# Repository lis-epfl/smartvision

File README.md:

# smartvision
SmartVision sensor

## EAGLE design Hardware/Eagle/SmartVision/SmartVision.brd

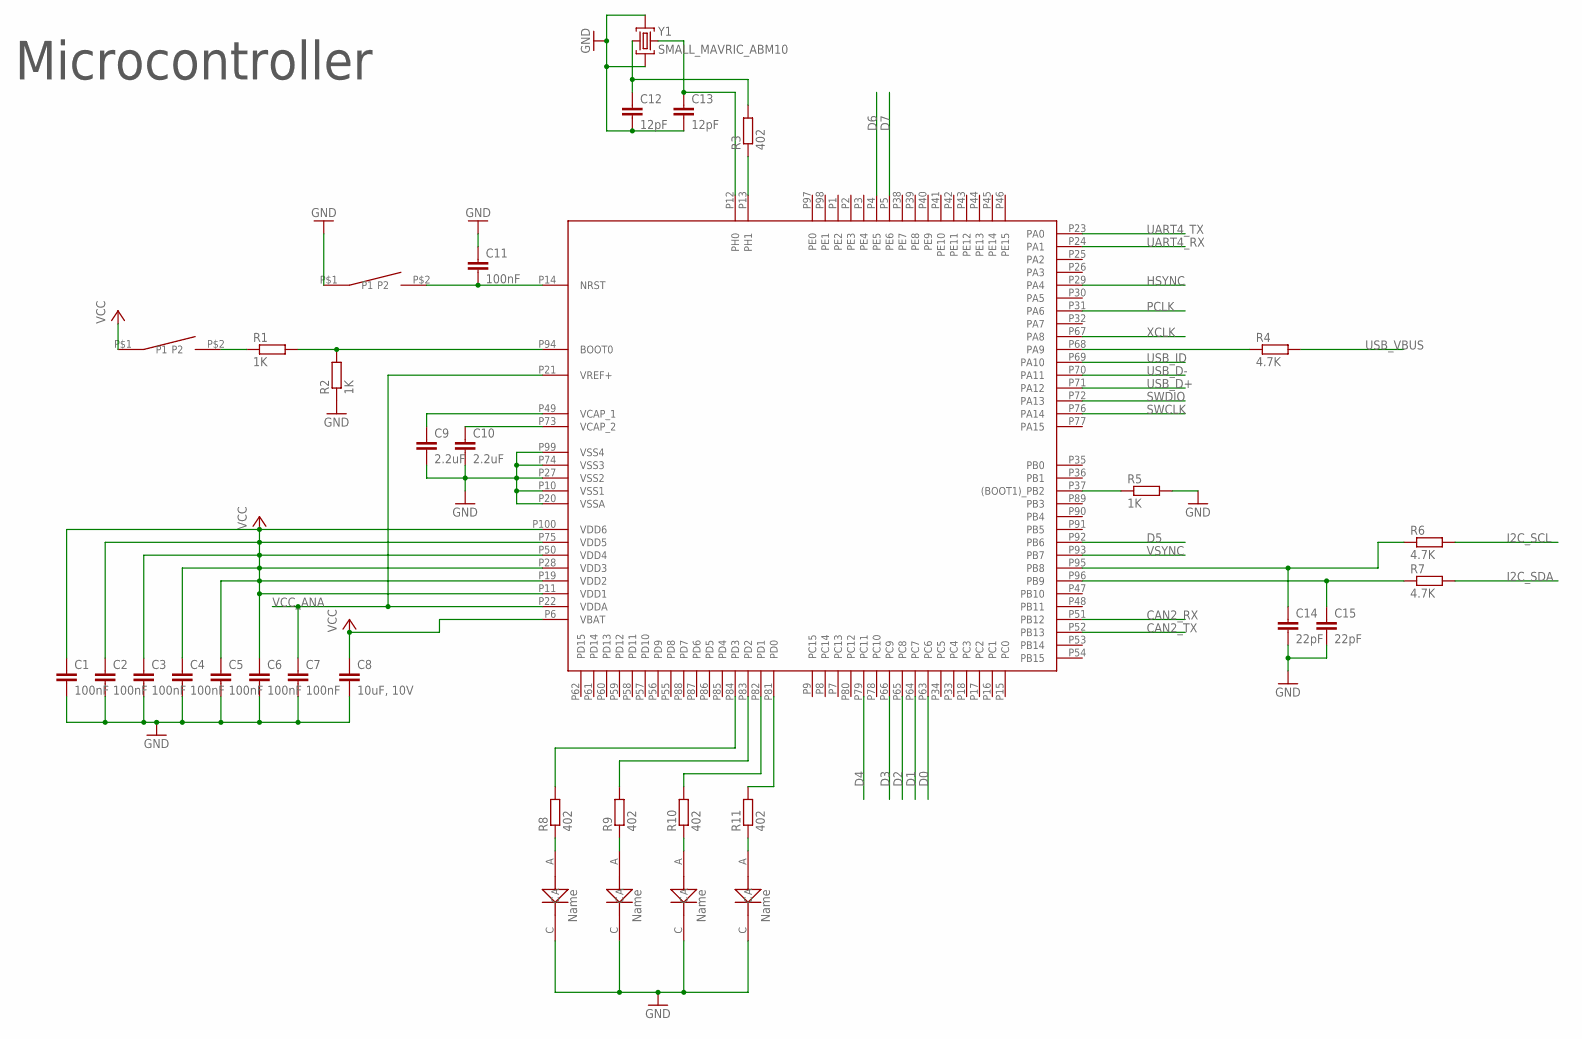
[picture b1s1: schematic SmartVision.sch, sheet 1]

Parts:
C1, C2, C3, C4, C5, C6, C7, C11: 100nF; SMALL_MAVRIC_SMALL_MAVRIC_CAPACITOR_C0402
C8: 10uF, 10V; SMALL_MAVRIC_SMALL_MAVRIC_CAPACITOR_C0603
C9, C10: 2.2uF; SMALL_MAVRIC_SMALL_MAVRIC_CAPACITOR_C0402
C12, C13: 12pF; SMALL_MAVRIC_SMALL_MAVRIC_CAPACITOR_C0402
C14, C15: 22pF; SMALL_MAVRIC_SMALL_MAVRIC_CAPACITOR_C0402
R1, R2, R5: 1K; SMALL_MAVRIC_SMALL_MAVRIC_RESISTOR_R0402
R3, R8, R9, R10, R11: 402; SMALL_MAVRIC_SMALL_MAVRIC_RESISTOR_R0402
R4, R6, R7: 4.7K; SMALL_MAVRIC_SMALL_MAVRIC_RESISTOR_R0402
U$1: STM32F407VGT6-100
U$29, U$31: SWITCH_OFF_(ON)
U$40, U$41, U$42, U$43: LED
Y1: SMALL_MAVRIC_ABM10; SMALL_MAVRIC_OSCILLATOR_ABM10

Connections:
CAN2_RX: U$1.P51 (PB12); also elsewhere on the board
CAN2_TX: U$1.P52 (PB13); also elsewhere on the board
D0: U$1.P63 (PC6); also elsewhere on the board
D1: U$1.P64 (PC7); also elsewhere on the board
D2: U$1.P65 (PC8); also elsewhere on the board
D3: U$1.P66 (PC9); also elsewhere on the board
D4: U$1.P79 (PC11); also elsewhere on the board
D5: U$1.P92 (PB6); also elsewhere on the board
D6: U$1.P4 (PE5); also elsewhere on the board
D7: U$1.P5 (PE6); also elsewhere on the board
GND: C1.2, C2.2, C3.2, C4.2, C5.2, C6.2, C7.2, C8.2, C9.2, C10.2, C11.1, C12.2, C13.2, C14.2, C15.2, R2.1, R5.2, U$1.P10 (VSS1), U$1.P20 (VSSA), U$1.P27 (VSS2), U$1.P74 (VSS3), U$1.P99 (VSS4), U$29.P$1 (P1), U$40.C, U$41.C, U$42.C, U$43.C, Y1.2, Y1.4; also elsewhere on the board
HSYNC: U$1.P29 (PA4); also elsewhere on the board
I2C_SCL: R6.2; also elsewhere on the board
I2C_SDA: R7.2; also elsewhere on the board
unnamed: R11.2, U$1.P81 (PD0)
unnamed: R10.2, U$1.P82 (PD1)
unnamed: R9.2, U$1.P83 (PD2)
unnamed: R8.2, U$1.P84 (PD3)
unnamed: C13.1, U$1.P12 (PH0), Y1.3
unnamed: R8.1, U$40.A
unnamed: C12.1, R3.2, Y1.1
unnamed: R9.1, U$41.A
unnamed: R10.1, U$42.A
unnamed: R3.1, U$1.P13 (PH1)
unnamed: C15.1, R7.1, U$1.P96 (PB9)
unnamed: C9.1, U$1.P49 (VCAP_1)
unnamed: C10.1, U$1.P73 (VCAP_2)
unnamed: C14.1, R6.1, U$1.P95 (PB8)
unnamed: R4.1, U$1.P68 (PA9)
unnamed: C11.2, U$1.P14 (NRST), U$29.P$2 (P2)
unnamed: R1.1, U$31.P$2 (P2)
unnamed: R1.2, R2.2, U$1.P94 (BOOT0)
unnamed: R5.1, U$1.P37 ((BOOT1)_PB2)
unnamed: R11.1, U$43.A
PCLK: U$1.P31 (PA6); also elsewhere on the board
SWCLK: U$1.P76 (PA14); also elsewhere on the board
SWDIO: U$1.P72 (PA13); also elsewhere on the board
UART4_RX: U$1.P24 (PA1); also elsewhere on the board
UART4_TX: U$1.P23 (PA0); also elsewhere on the board
USB_D+: U$1.P71 (PA12); also elsewhere on the board
USB_D-: U$1.P70 (PA11); also elsewhere on the board
USB_ID: U$1.P69 (PA10); also elsewhere on the board
USB_VBUS: R4.2; also elsewhere on the board
VCC: C1.1, C2.1, C3.1, C4.1, C5.1, C6.1, C8.1, U$1.P6 (VBAT), U$1.P11 (VDD1), U$1.P19 (VDD2), U$1.P28 (VDD3), U$1.P50 (VDD4), U$1.P75 (VDD5), U$1.P100 (VDD6), U$31.P$1 (P1); also elsewhere on the board
VCC_ANA: C7.1, U$1.P21 (VREF+), U$1.P22 (VDDA); also elsewhere on the board
VSYNC: U$1.P93 (PB7); also elsewhere on the board
XCLK: U$1.P67 (PA8); also elsewhere on the board

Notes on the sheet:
Microcontroller

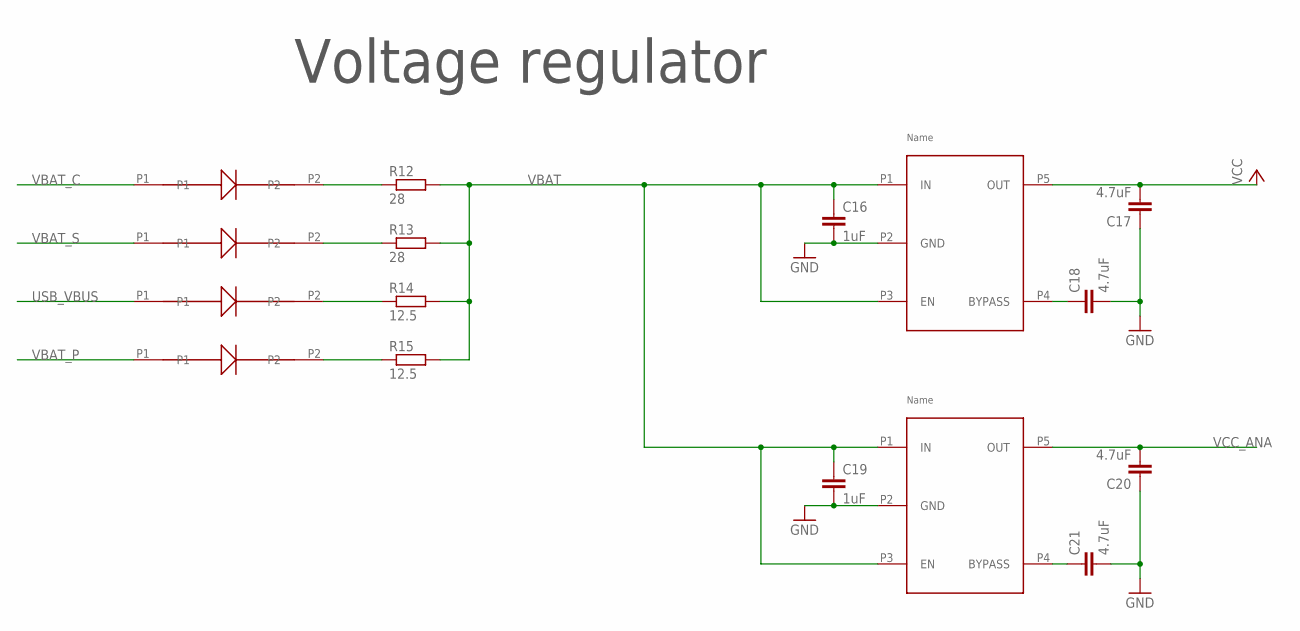
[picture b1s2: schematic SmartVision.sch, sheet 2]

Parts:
C16, C19: 1uF; SMALL_MAVRIC_SMALL_MAVRIC_CAPACITOR_C0402
C17, C18, C20, C21: 4.7uF; SMALL_MAVRIC_SMALL_MAVRIC_CAPACITOR_C0603
R12, R13: 28; SMALL_MAVRIC_SMALL_MAVRIC_RESISTOR_R0402
R14, R15: 12.5; SMALL_MAVRIC_SMALL_MAVRIC_RESISTOR_R0402
U$2, U$7: VOLTAGE_REGULATOR_3V
U$54, U$55, U$57, U$61: DIODE_SCHOTTKY

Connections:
GND: C16.2, C17.1, C18.2, C19.2, C20.1, C21.2, U$2.P2 (GND), U$7.P2 (GND); also elsewhere on the board
unnamed: C21.1, U$7.P4 (BYPASS)
unnamed: C18.1, U$2.P4 (BYPASS)
unnamed: R13.1, U$61.P2
unnamed: R15.1, U$54.P2
unnamed: R12.1, U$55.P2
unnamed: R14.1, U$57.P2
USB_VBUS: U$57.P1; also elsewhere on the board
VBAT: C16.1, C19.1, R12.2, R13.2, R14.2, R15.2, U$2.P1 (IN), U$2.P3 (EN), U$7.P1 (IN), U$7.P3 (EN); also elsewhere on the board
VBAT_C: U$55.P1; also elsewhere on the board
VBAT_P: U$54.P1; also elsewhere on the board
VBAT_S: U$61.P1; also elsewhere on the board
VCC: C17.2, U$2.P5 (OUT); also elsewhere on the board
VCC_ANA: C20.2, U$7.P5 (OUT); also elsewhere on the board

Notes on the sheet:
Voltage regulator

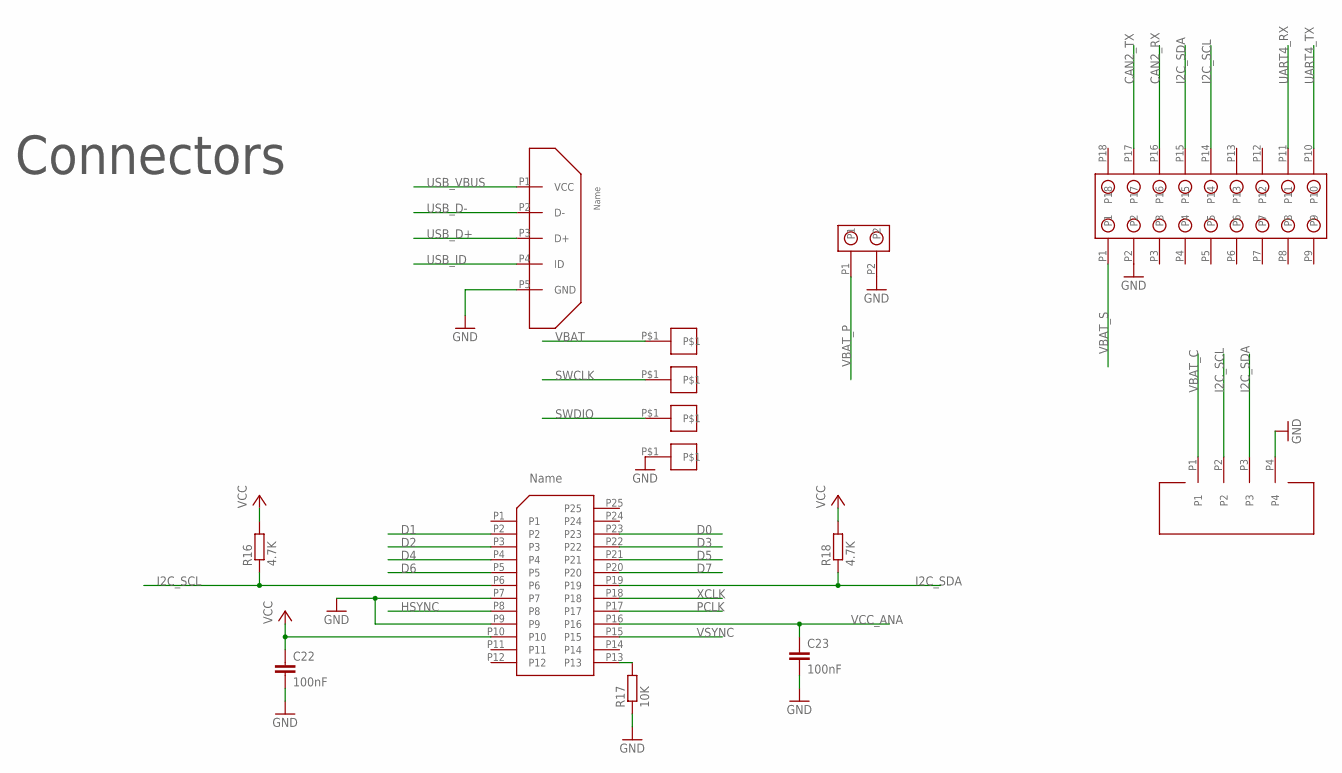
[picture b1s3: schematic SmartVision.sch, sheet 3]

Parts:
C22, C23: 100nF; SMALL_MAVRIC_SMALL_MAVRIC_CAPACITOR_C0402
R16, R18: 4.7K; SMALL_MAVRIC_SMALL_MAVRIC_RESISTOR_R0402
R17: 10K; SMALL_MAVRIC_SMALL_MAVRIC_RESISTOR_R0402
U$3, U$5, U$63, U$64: PAD_FLASH
U$4: MICRO_USB_PLUG
U$11: CON_CAMERA_FPC_25P_0.3MM
U$52: CON_2.54MM_18PINS_STACKABLE
U$53: CON_1.25MM_4PINS
U$59: CON_2.54MM_2PINS

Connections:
CAN2_RX: U$52.P16; also elsewhere on the board
CAN2_TX: U$52.P17; also elsewhere on the board
D0: U$11.P23; also elsewhere on the board
D1: U$11.P2; also elsewhere on the board
D2: U$11.P3; also elsewhere on the board
D3: U$11.P22; also elsewhere on the board
D4: U$11.P4; also elsewhere on the board
D5: U$11.P21; also elsewhere on the board
D6: U$11.P5; also elsewhere on the board
D7: U$11.P20; also elsewhere on the board
GND: C22.2, C23.2, R17.1, U$3.P$1, U$4.P5 (GND), U$11.P7, U$11.P9, U$52.P2, U$53.P4, U$59.P2; also elsewhere on the board
HSYNC: U$11.P8; also elsewhere on the board
I2C_SCL: R16.1, U$11.P6, U$52.P14, U$53.P2; also elsewhere on the board
I2C_SDA: R18.1, U$11.P19, U$52.P15, U$53.P3; also elsewhere on the board
unnamed: R17.2, U$11.P13
PCLK: U$11.P17; also elsewhere on the board
SWCLK: U$63.P$1; also elsewhere on the board
SWDIO: U$64.P$1; also elsewhere on the board
UART4_RX: U$52.P11; also elsewhere on the board
UART4_TX: U$52.P10; also elsewhere on the board
USB_D+: U$4.P3 (D+); also elsewhere on the board
USB_D-: U$4.P2 (D-); also elsewhere on the board
USB_ID: U$4.P4 (ID); also elsewhere on the board
USB_VBUS: U$4.P1 (VCC); also elsewhere on the board
VBAT: U$5.P$1; also elsewhere on the board
VBAT_C: U$53.P1; also elsewhere on the board
VBAT_P: U$59.P1; also elsewhere on the board
VBAT_S: U$52.P1; also elsewhere on the board
VCC: C22.1, R16.2, R18.2, U$11.P10; also elsewhere on the board
VCC_ANA: C23.1, U$11.P16; also elsewhere on the board
VSYNC: U$11.P15; also elsewhere on the board
XCLK: U$11.P18; also elsewhere on the board

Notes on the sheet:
Connectors

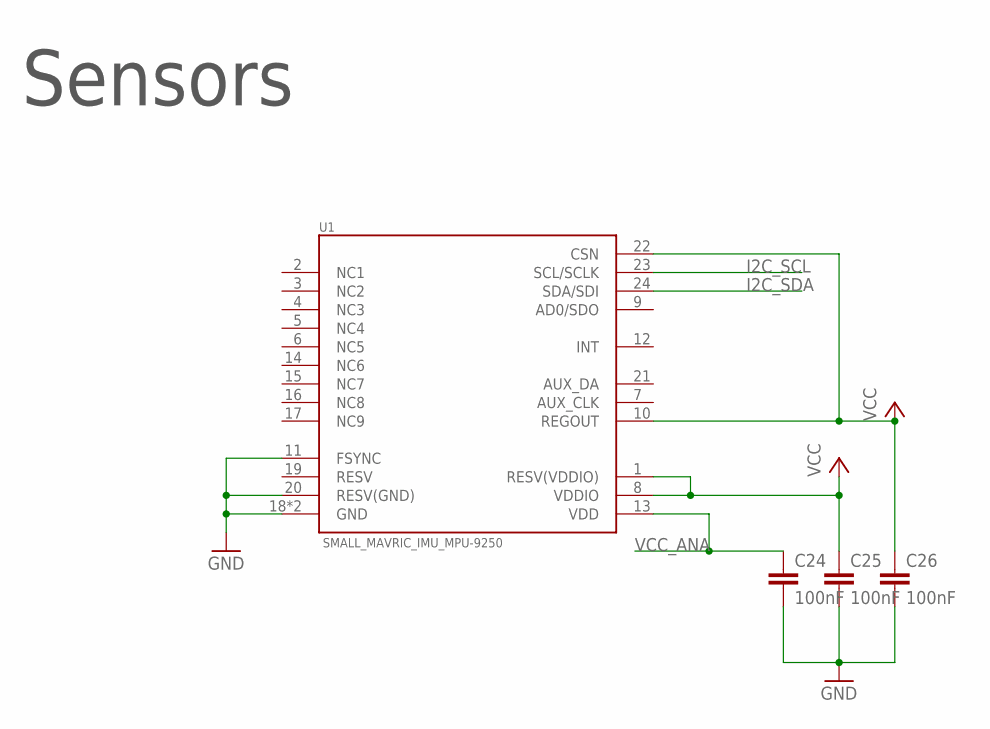
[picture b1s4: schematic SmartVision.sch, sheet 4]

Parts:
C24, C25, C26: 100nF; SMALL_MAVRIC_SMALL_MAVRIC_CAPACITOR_C0402
U1: SMALL_MAVRIC_IMU_MPU-9250; SMALL_MAVRIC_SMALL_MAVRIC_QFN-24_3.0X3.0MM

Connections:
GND: C24.2, C25.2, C26.2, U1.11 (FSYNC), U1.18 (GND), U1.20 (RESV(GND)), U1.CENTRAL_PAD (GND); also elsewhere on the board
I2C_SCL: U1.23 (SCL/SCLK); also elsewhere on the board
I2C_SDA: U1.24 (SDA/SDI); also elsewhere on the board
VCC: C25.1, C26.1, U1.1 (RESV(VDDIO)), U1.8 (VDDIO), U1.10 (REGOUT), U1.22 (CSN); also elsewhere on the board
VCC_ANA: C24.1, U1.13 (VDD); also elsewhere on the board

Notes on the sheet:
Sensors

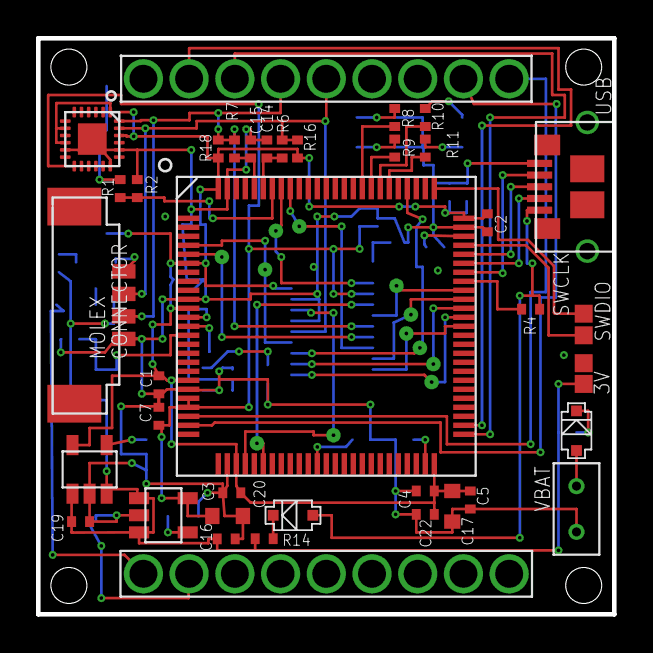
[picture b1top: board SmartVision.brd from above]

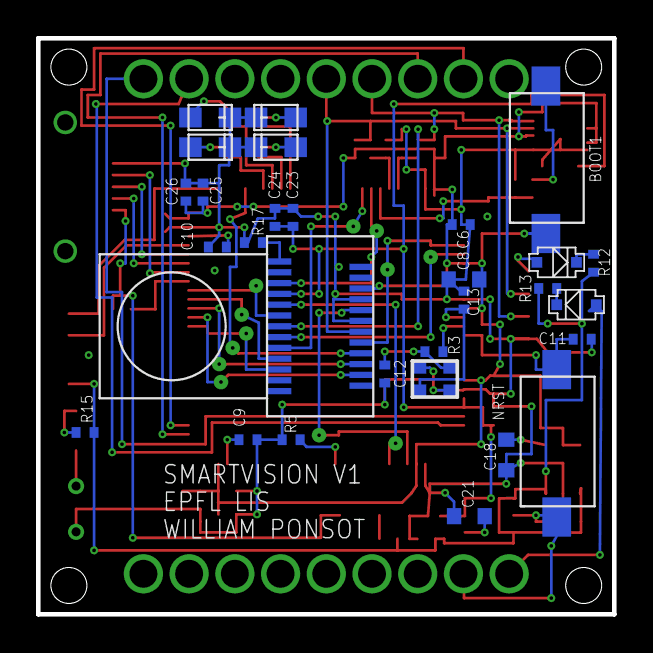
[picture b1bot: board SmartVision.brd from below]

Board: 2 copper layers, 32.0 x 32.0 mm, 68 parts (29 on the bottom side), 58 nets.

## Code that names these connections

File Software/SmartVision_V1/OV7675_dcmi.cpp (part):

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// Varible to configure the camera
uint32_t line = 0;
uint32_t line_Frame = 0;
uint32_t vsync = 0;

/**
  * @brief  Initializes the hardware resources (I2C and GPIO) used to configure 
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	uint32_t data_remaining;
	uint32_t capture;
	
	HAL_RCC_MCOConfig(RCC_MCO1, RCC_MCO1SOURCE_HSE, RCC_MCODIV_1); // Main Clock Output 8Mhz to PA8
	
	// I2C
	OV7675_I2C_config();
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	__HAL_RCC_DCMI_CLK_ENABLE(); // Clock DCMI
	__HAL_RCC_DMA2_CLK_ENABLE(); // Clock DMA2
	
	// D0 (PC6), D1 (PC7), D2 (PC8), D3 (PC9), D4 (PC11)
	__HAL_RCC_GPIOC_CLK_ENABLE(); // Clock port C enable
	GPIO_InitStructure.Pin = GPIO_PIN_6 | GPIO_PIN_7 | GPIO_PIN_8 | GPIO_PIN_9 | GPIO_PIN_11;
	GPIO_InitStructure.Mode = GPIO_MODE_AF_OD;
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	GPIO_InitStructure.Alternate = GPIO_AF13_DCMI; 
	HAL_GPIO_Init(GPIOC, &GPIO_InitStructure);
	
	// D5 (PB6), Vsync (PB7)
	__HAL_RCC_GPIOB_CLK_ENABLE(); // Clock port B enable
	GPIO_InitStructure.Pin = GPIO_PIN_6 | GPIO_PIN_7;
	HAL_GPIO_Init(GPIOB, &GPIO_InitStructure);
	
	// D6 (PE5), D7 (PE6)
	__HAL_RCC_GPIOE_CLK_ENABLE(); // Clock port B enable
	GPIO_InitStructure.Pin = GPIO_PIN_5 | GPIO_PIN_6;
	HAL_GPIO_Init(GPIOE, &GPIO_InitStructure);
	
	// Hsync (PA4), Pxclk (PA6)
	__HAL_RCC_GPIOA_CLK_ENABLE(); // Clock port B enable
	GPIO_InitStructure.Pin = GPIO_PIN_4 | GPIO_PIN_6;
	HAL_GPIO_Init(GPIOA, &GPIO_InitStructure);
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{
	line_Frame = line;
	line = 0;
	vsync = 0;
	asm("bkpt 255");
}

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
void HAL_DCMI_VsyncEventCallback(DCMI_HandleTypeDef *hdcmi)
{
	vsync = 1;
}

extern "C" void DCMI_IRQHandler(void)   
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
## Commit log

2016-07-11 Add files from William's repository
2016-07-18 Remove useless software in order to clean the directory
2016-07-18 Visual GDB code
2016-07-21 Mavlink connection with heatbeat sended without convinience functions
2016-07-21 Mavlink convenience functions worked. Heartbeat sended !
2016-07-25 Parameters sended to QGround station (worked in both way). Need to solve image problem due to data format
2016-07-27 Image (grayscale) sended. Take a picture each time a camera parameter is changed
2016-07-28 Add .gitignore
2016-07-28 More cleanup
2016-07-28 Remove db
2016-07-28 Apply changes from broken repository
2016-07-28 Fix gitmodule
2016-07-28 Remove BS
2016-07-28 Update gitignore
2016-08-22 Change to QVGA, RGB565, add some helper methods for register setting
2016-08-22 Add commented out register fiddling attempts
2016-08-22 add report
